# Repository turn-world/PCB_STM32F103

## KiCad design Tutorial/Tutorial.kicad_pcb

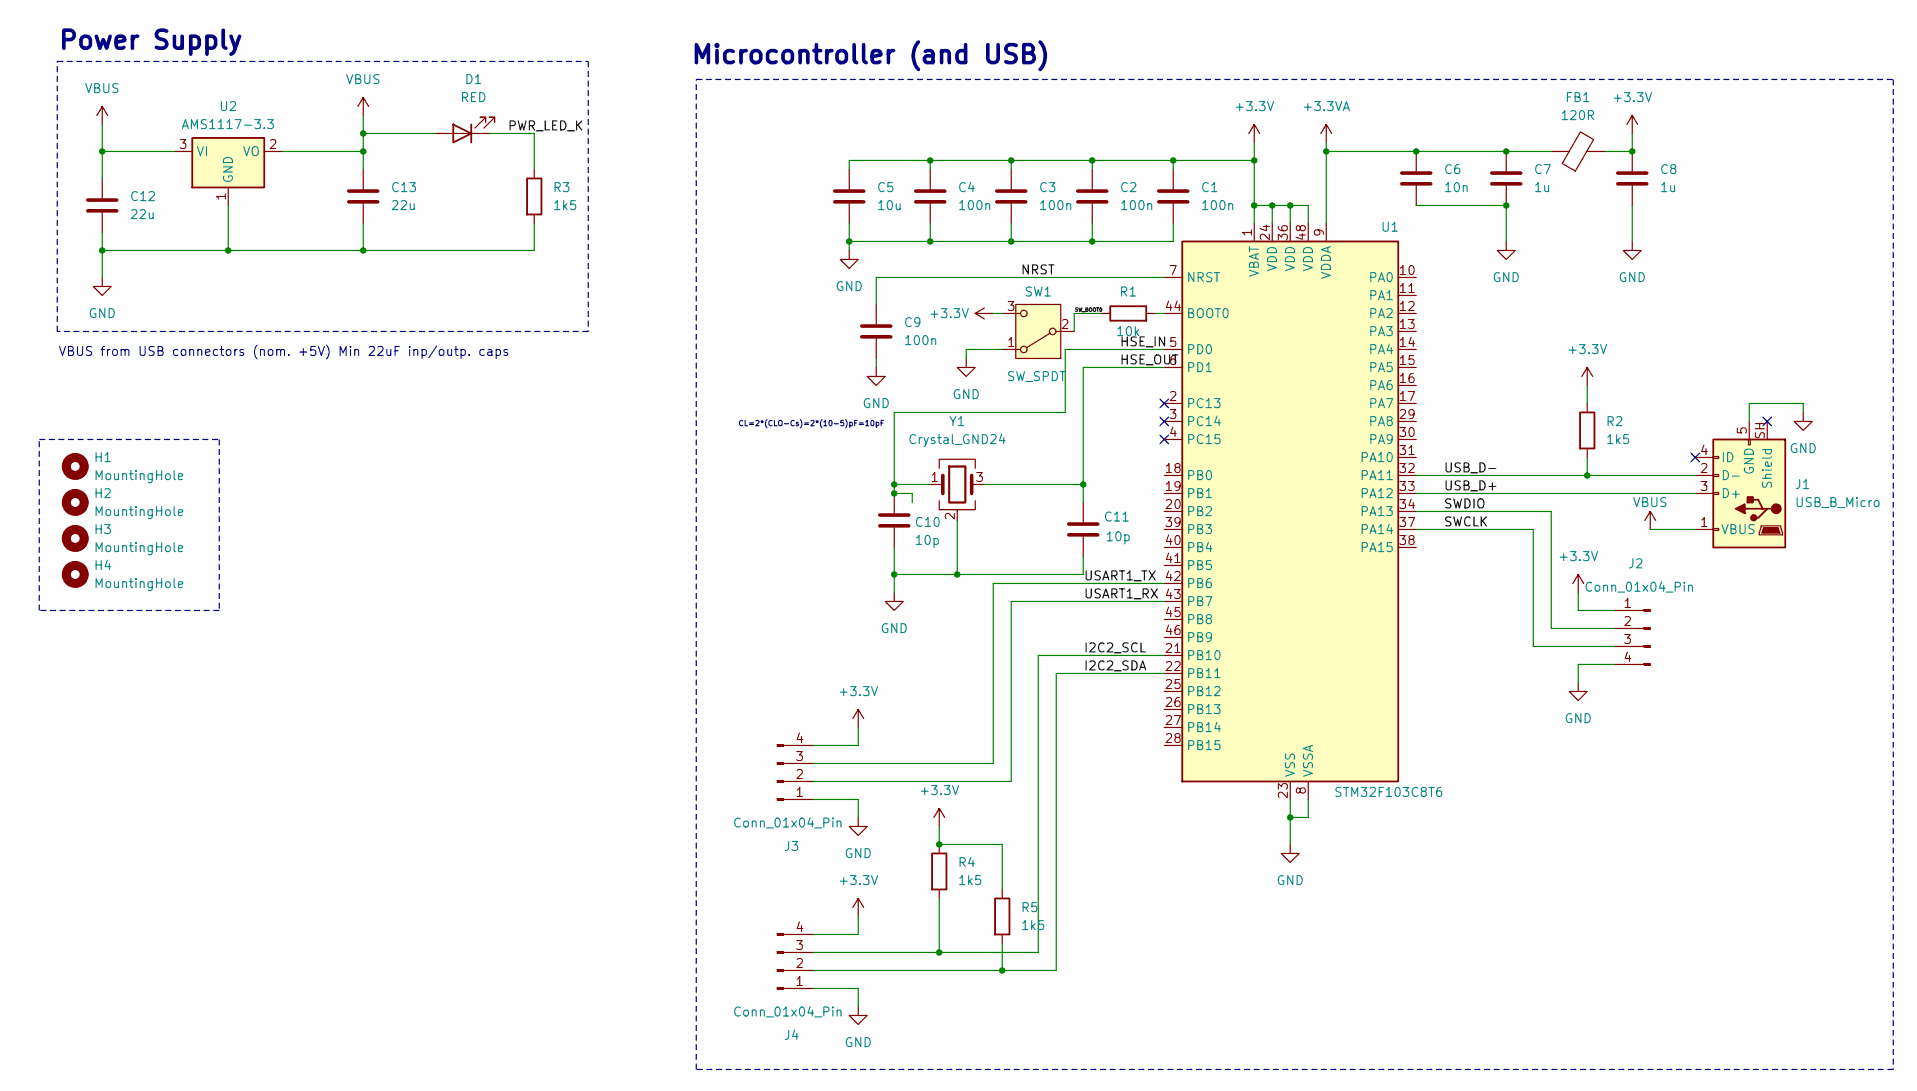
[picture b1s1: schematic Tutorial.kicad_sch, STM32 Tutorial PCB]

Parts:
C1, C2, C3, C4, C9: 100n; C_0402_1005Metric
C5: 10u; C_0603_1608Metric
C6: 10n; C_0402_1005Metric
C7, C8: 1u; C_0402_1005Metric
C10, C11: 10p; C_0402_1005Metric
C12, C13: 22u; C_0805_2012Metric
D1: RED; LED_0603_1608Metric
FB1: 120R; L_0603_1608Metric
H1, H2, H3, H4: MountingHole; MountingHole_2.2mm_M2
J1: USB_B_Micro; USB_Micro-B_Wuerth_629105150521
J2, J3, J4: Conn_01x04_Pin; PinHeader_1x04_P2.54mm_Vertical
R1: 10k; R_0402_1005Metric
R2, R3, R4, R5: 1k5; R_0402_1005Metric
SW1: SW_SPDT; SW_SPDT_PCM12
U1: STM32F103C8T6; LQFP-48_7x7mm_P0.5mm
U2: AMS1117-3.3; SOT-223-3_TabPin2
Y1: Crystal_GND24; Crystal_SMD_3225-4Pin_3.2x2.5mm

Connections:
+3.3V: C1.1, C2.1, C3.1, C4.1, C5.1, C8.1, FB1.2, J2.1, J3.4, J4.4, R2.1, R4.1, R5.1, SW1.3 (C), U1.1 (VBAT), U1.24 (VDD), U1.36 (VDD), U1.48 (VDD)
+3.3VA: C6.1, C7.1, FB1.1, U1.9 (VDDA)
/HSE_IN: C10.1, U1.5 (PD0), Y1.1
/HSE_OUT: C11.1, U1.6 (PD1), Y1.3
/I2C2_SCL: J4.3, R4.2, U1.21 (PB10)
/I2C2_SDA: J4.2, R5.2, U1.22 (PB11)
/NRST: C9.1, U1.7 (NRST)
/PWR_LED_K: D1.1 (K), R3.1
/SWCLK: J2.3, U1.37 (PA14)
/SWDIO: J2.2, U1.34 (PA13)
/SW_BOOT0: R1.1, SW1.2 (B)
/USART1_RX: J3.2, U1.43 (PB7)
/USART1_TX: J3.3, U1.42 (PB6)
/USB_D+: J1.3 (D+), U1.33 (PA12)
/USB_D-: J1.2 (D-), R2.2, U1.32 (PA11)
GND: C1.2, C2.2, C3.2, C4.2, C5.2, C6.2, C7.2, C8.2, C9.2, C10.2, C11.2, C12.2, C13.2, J1.5 (GND), J2.4, J3.1, J4.1, R3.2, SW1.1 (A), U1.8 (VSSA), U1.23 (VSS), U1.35 (VSS), U1.47 (VSS), U2.1 (GND), Y1.2 (G), Y1.4 (G)
unnamed: R1.2, U1.44 (BOOT0)
VBUS: C12.1, C13.1, D1.2 (A), J1.1 (VBUS), U2.2 (VO), U2.3 (VI)

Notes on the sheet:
Microcontroller (and USB)
VBUS from USB connectors (nom. +5V) Min 22uF inp/outp. caps
Power Supply
CL=2*(CLO-Cs)=2*(10-5)pF=10pF

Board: 2 copper layers, 32 parts (0 on the bottom side), 18 nets, no tracks yet.
